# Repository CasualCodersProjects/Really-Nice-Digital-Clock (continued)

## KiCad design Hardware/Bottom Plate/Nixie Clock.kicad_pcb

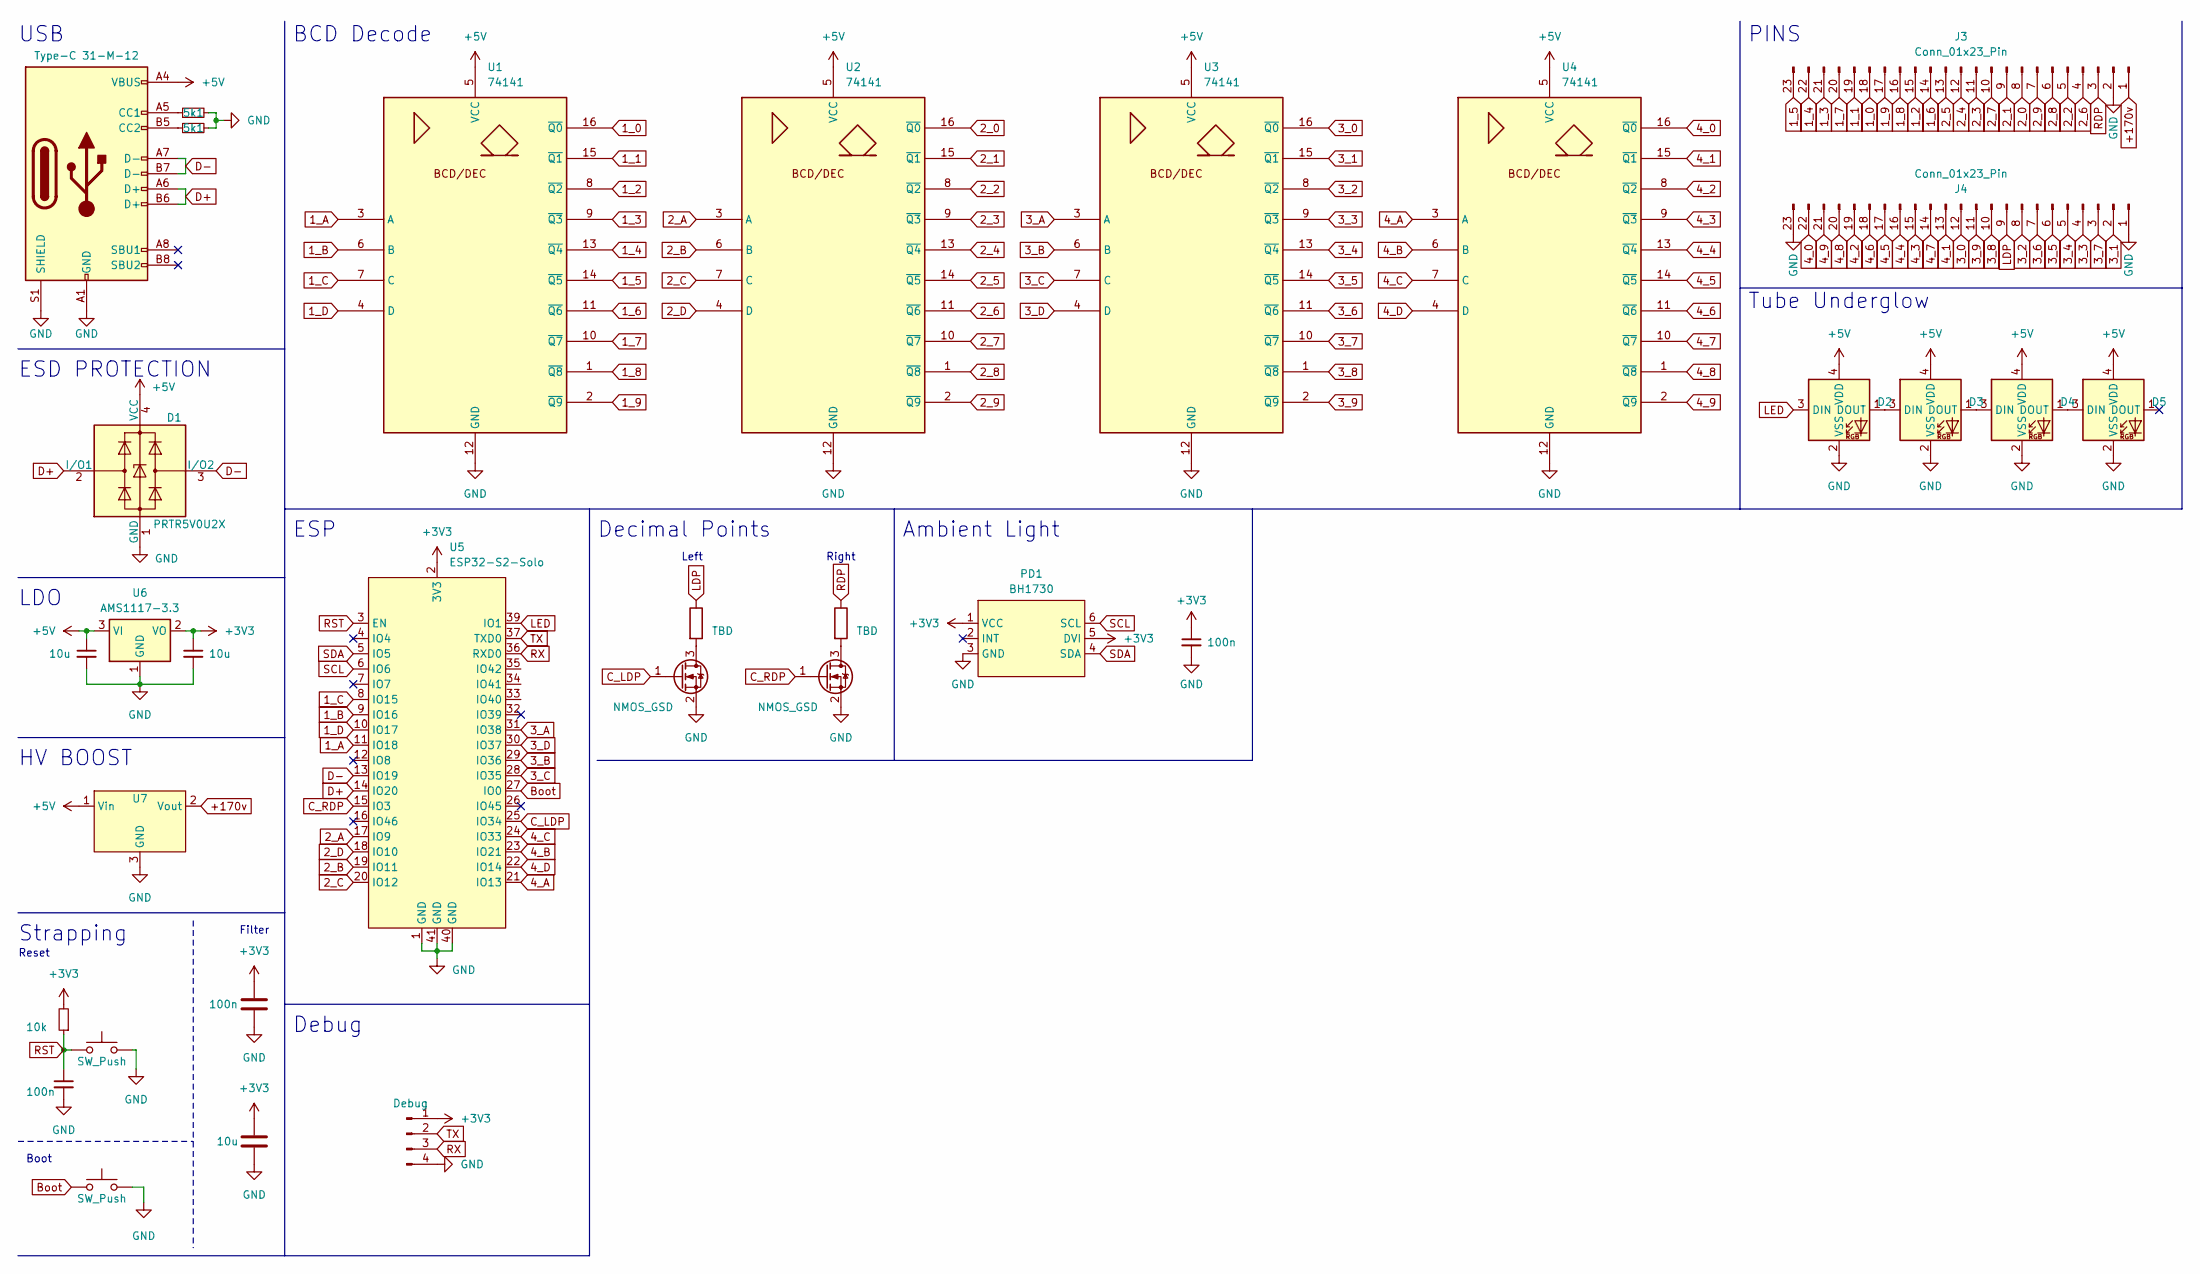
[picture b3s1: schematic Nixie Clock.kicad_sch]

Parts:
C1, C2, C3: 10u; C_0603_1608Metric
C4, C5, C6: 100n; C_0402_1005Metric
D1: PRTR5V0U2X; SOT-143
D2, D3, D4, D5: LED_WS2812B-2020_PLCC4_2.0x2.0mm
J1: Type-C 31-M-12; USB_C_Receptacle_HRO_TYPE-C-31-M-12
J2: Debug; PinHeader_1x04_P2.54mm_Vertical
J3, J4: Conn_01x23_Pin; PinSocket_1x23_P2.54mm_Vertical
PD1: BH1730; WSOF6
Q1, Q2: NMOS_GSD; SOT-23
R1, R2: 5k1; R_0402_1005Metric
R3: 10k; R_0402_1005Metric
R4, R5: TBD; R_0603_1608Metric_Pad0.98x0.95mm_HandSolder
RST1: SW_Push; SW_SPST_SKQG_WithStem
SW2: SW_Push; SW_SPST_SKQG_WithStem
U1, U2, U3, U4: 74141; DIP-16_W7.62mm
U5: ESP32-S2-Solo; ESP32-S3-WROOM-1
U6: AMS1117-3.3; SOT-223-3_TabPin2
U7: 8200HV

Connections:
1_0: J3.18, U1.16 (~Q0)
1_1: J3.19, U1.15 (~Q1)
1_2: J3.15, U1.8 (~Q2)
1_3: J3.21, U1.9 (~Q3)
1_4: J3.22, U1.13 (~Q4)
1_5: J3.23, U1.14 (~Q5)
1_6: J3.14, U1.11 (~Q6)
1_7: J3.20, U1.10 (~Q7)
1_8: J3.16, U1.1 (~Q8)
1_9: J3.17, U1.2 (~Q9)
1_A: U1.3 (A), U5.11 (IO18)
1_B: U1.6 (B), U5.9 (IO16)
1_C: U1.7 (C), U5.8 (IO15)
1_D: U1.4 (D), U5.10 (IO17)
2_0: J3.8, U2.16 (~Q0)
2_1: J3.9, U2.15 (~Q1)
2_2: J3.5, U2.8 (~Q2)
2_3: J3.11, U2.9 (~Q3)
2_4: J3.12, U2.13 (~Q4)
2_5: J3.13, U2.14 (~Q5)
2_6: J3.4, U2.11 (~Q6)
2_7: J3.10, U2.10 (~Q7)
2_8: J3.6, U2.1 (~Q8)
2_9: J3.7, U2.2 (~Q9)
2_A: U2.3 (A), U5.17 (IO9)
2_B: U2.6 (B), U5.19 (IO11)
2_C: U2.7 (C), U5.20 (IO12)
2_D: U2.4 (D), U5.18 (IO10)
3_0: J4.12, U3.16 (~Q0)
3_1: J4.2, U3.15 (~Q1)
3_2: J4.8, U3.8 (~Q2)
3_3: J4.4, U3.9 (~Q3)
3_4: J4.5, U3.13 (~Q4)
3_5: J4.6, U3.14 (~Q5)
3_6: J4.7, U3.11 (~Q6)
3_7: J4.3, U3.10 (~Q7)
3_8: J4.10, U3.1 (~Q8)
3_9: J4.11, U3.2 (~Q9)
3_A: U3.3 (A), U5.31 (IO38)
3_B: U3.6 (B), U5.29 (IO36)
3_C: U3.7 (C), U5.28 (IO35)
3_D: U3.4 (D), U5.30 (IO37)
4_0: J4.22, U4.16 (~Q0)
4_1: J4.13, U4.15 (~Q1)
4_2: J4.19, U4.8 (~Q2)
4_3: J4.15, U4.9 (~Q3)
4_4: J4.16, U4.13 (~Q4)
4_5: J4.17, U4.14 (~Q5)
4_6: J4.18, U4.11 (~Q6)
4_7: J4.14, U4.10 (~Q7)
4_8: J4.20, U4.1 (~Q8)
4_9: J4.21, U4.2 (~Q9)
4_A: U4.3 (A), U5.21 (IO13)
4_B: U4.6 (B), U5.23 (IO21)
4_C: U4.7 (C), U5.24 (IO33)
4_D: U4.4 (D), U5.22 (IO14)
+3V3: C2.1, C3.1, C4.1, C6.1, J2.1, PD1.1 (VCC), PD1.5 (DVI), R3.2, U5.2 (3V3), U6.2 (VO)
+5V: C1.1, D1.4 (VCC), D2.4 (VDD), D3.4 (VDD), D4.4 (VDD), D5.4 (VDD), J1.A4 (VBUS), J1.A9 (VBUS), J1.B4 (VBUS), J1.B9 (VBUS), U1.5 (VCC), U2.5 (VCC), U3.5 (VCC), U4.5 (VCC), U6.3 (VI), U7.1 (Vin)
+170v: J3.1, U7.2 (Vout)
C_LDP: Q2.1 (G), U5.25 (IO34)
C_RDP: Q1.1 (G), U5.15 (IO3)
D+: D1.2 (I/O1), J1.A6 (D+), J1.B6 (D+), U5.14 (IO20)
D-: D1.3 (I/O2), J1.A7 (D-), J1.B7 (D-), U5.13 (IO19)
GND: C1.2, C2.2, C3.2, C4.2, C5.2, C6.2, D1.1 (GND), D2.2 (VSS), D3.2 (VSS), D4.2 (VSS), D5.2 (VSS), J1.A1 (GND), J1.A12 (GND), J1.B1 (GND), J1.B12 (GND), J1.S1 (SHIELD), J2.4, J3.2, J4.1, J4.23, PD1.3 (GND), Q1.2 (S), Q2.2 (S), R1.2, R2.2, SW2.2, U1.12 (GND), U2.12 (GND), U3.12 (GND), U4.12 (GND), U5.1 (GND), U5.40 (GND), U5.41 (GND), U6.1 (GND), U7.3 (GND); also elsewhere on the board
LDP: J4.9, R5.1
LED: D2.3 (DIN), U5.39 (IO1)
unnamed: D2.1 (DOUT), D3.3 (DIN)
unnamed: D3.1 (DOUT), D4.3 (DIN)
unnamed: D4.1 (DOUT), D5.3 (DIN)
unnamed: J1.A5 (CC1), R1.1
unnamed: J1.B5 (CC2), R2.1
unnamed: Q1.3 (D), R4.2
unnamed: Q2.3 (D), R5.2
RDP: J3.3, R4.1
RX: J2.3, U5.36 (RXD0)
SCL: PD1.6 (SCL), U5.6 (IO6)
SDA: PD1.4 (SDA), U5.5 (IO5)
TX: J2.2, U5.37 (TXD0)

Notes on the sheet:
USB
Right
ESP
LDO
Strapping
Tube Underglow
Boot
HV BOOST
Reset
BCD Decode
Left
PINS
Decimal Points
Filter
Ambient Light
Debug
ESD PROTECTION

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
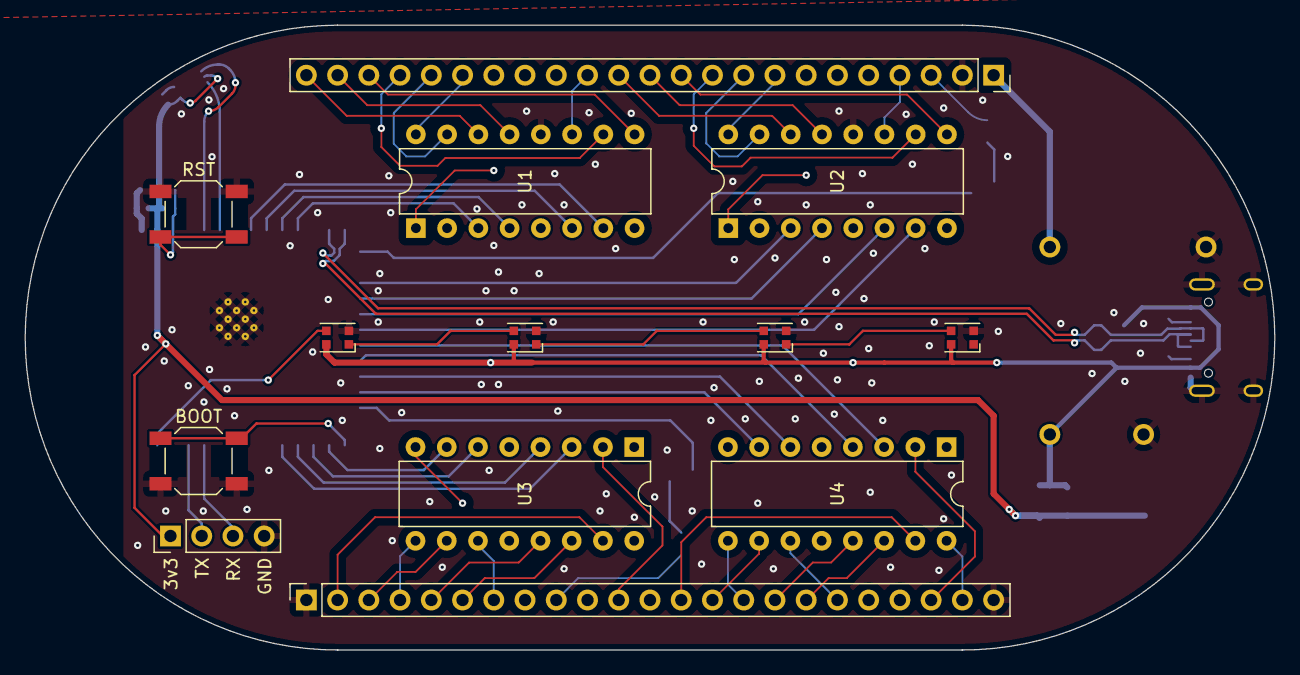
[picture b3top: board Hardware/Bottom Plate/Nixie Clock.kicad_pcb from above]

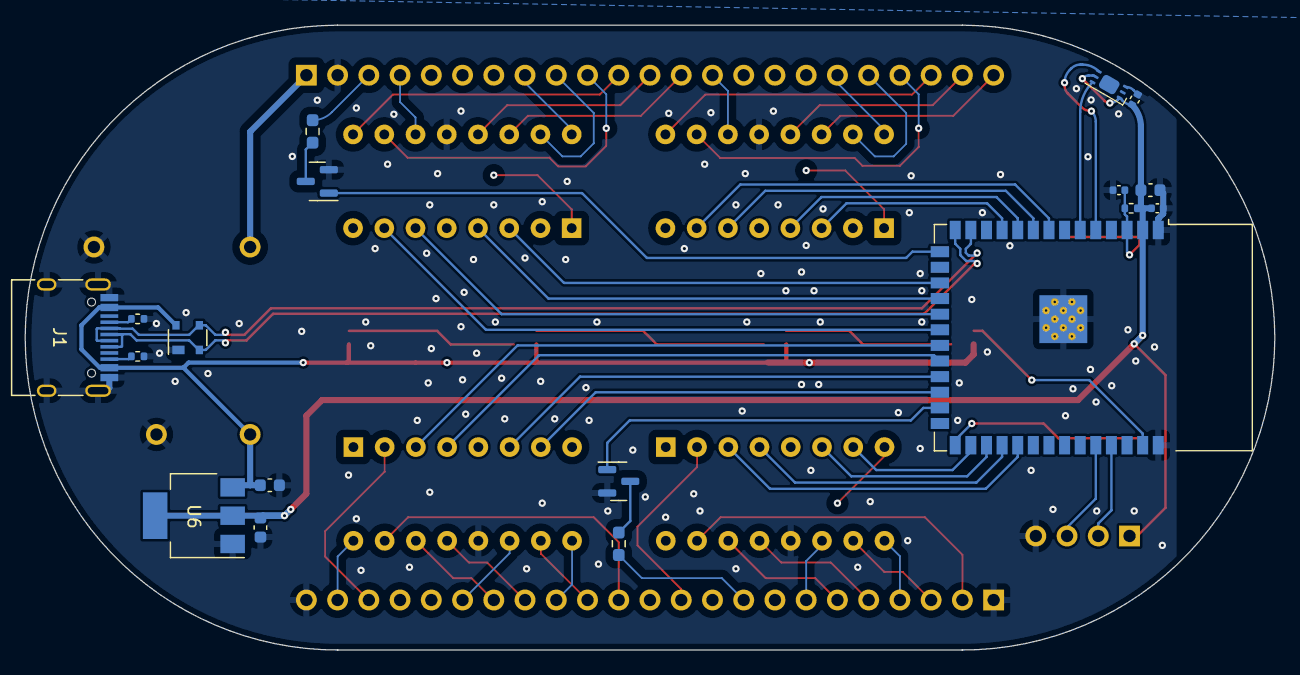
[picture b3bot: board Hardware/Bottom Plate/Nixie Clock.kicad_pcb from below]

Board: 4 copper layers, 101.6 x 50.8 mm, 32 parts (18 on the bottom side), 80 nets.

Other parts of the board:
SW1: SW_Push; SW_SPST_SKQG_WithStem

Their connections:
GND: SW1.2; also elsewhere on the board

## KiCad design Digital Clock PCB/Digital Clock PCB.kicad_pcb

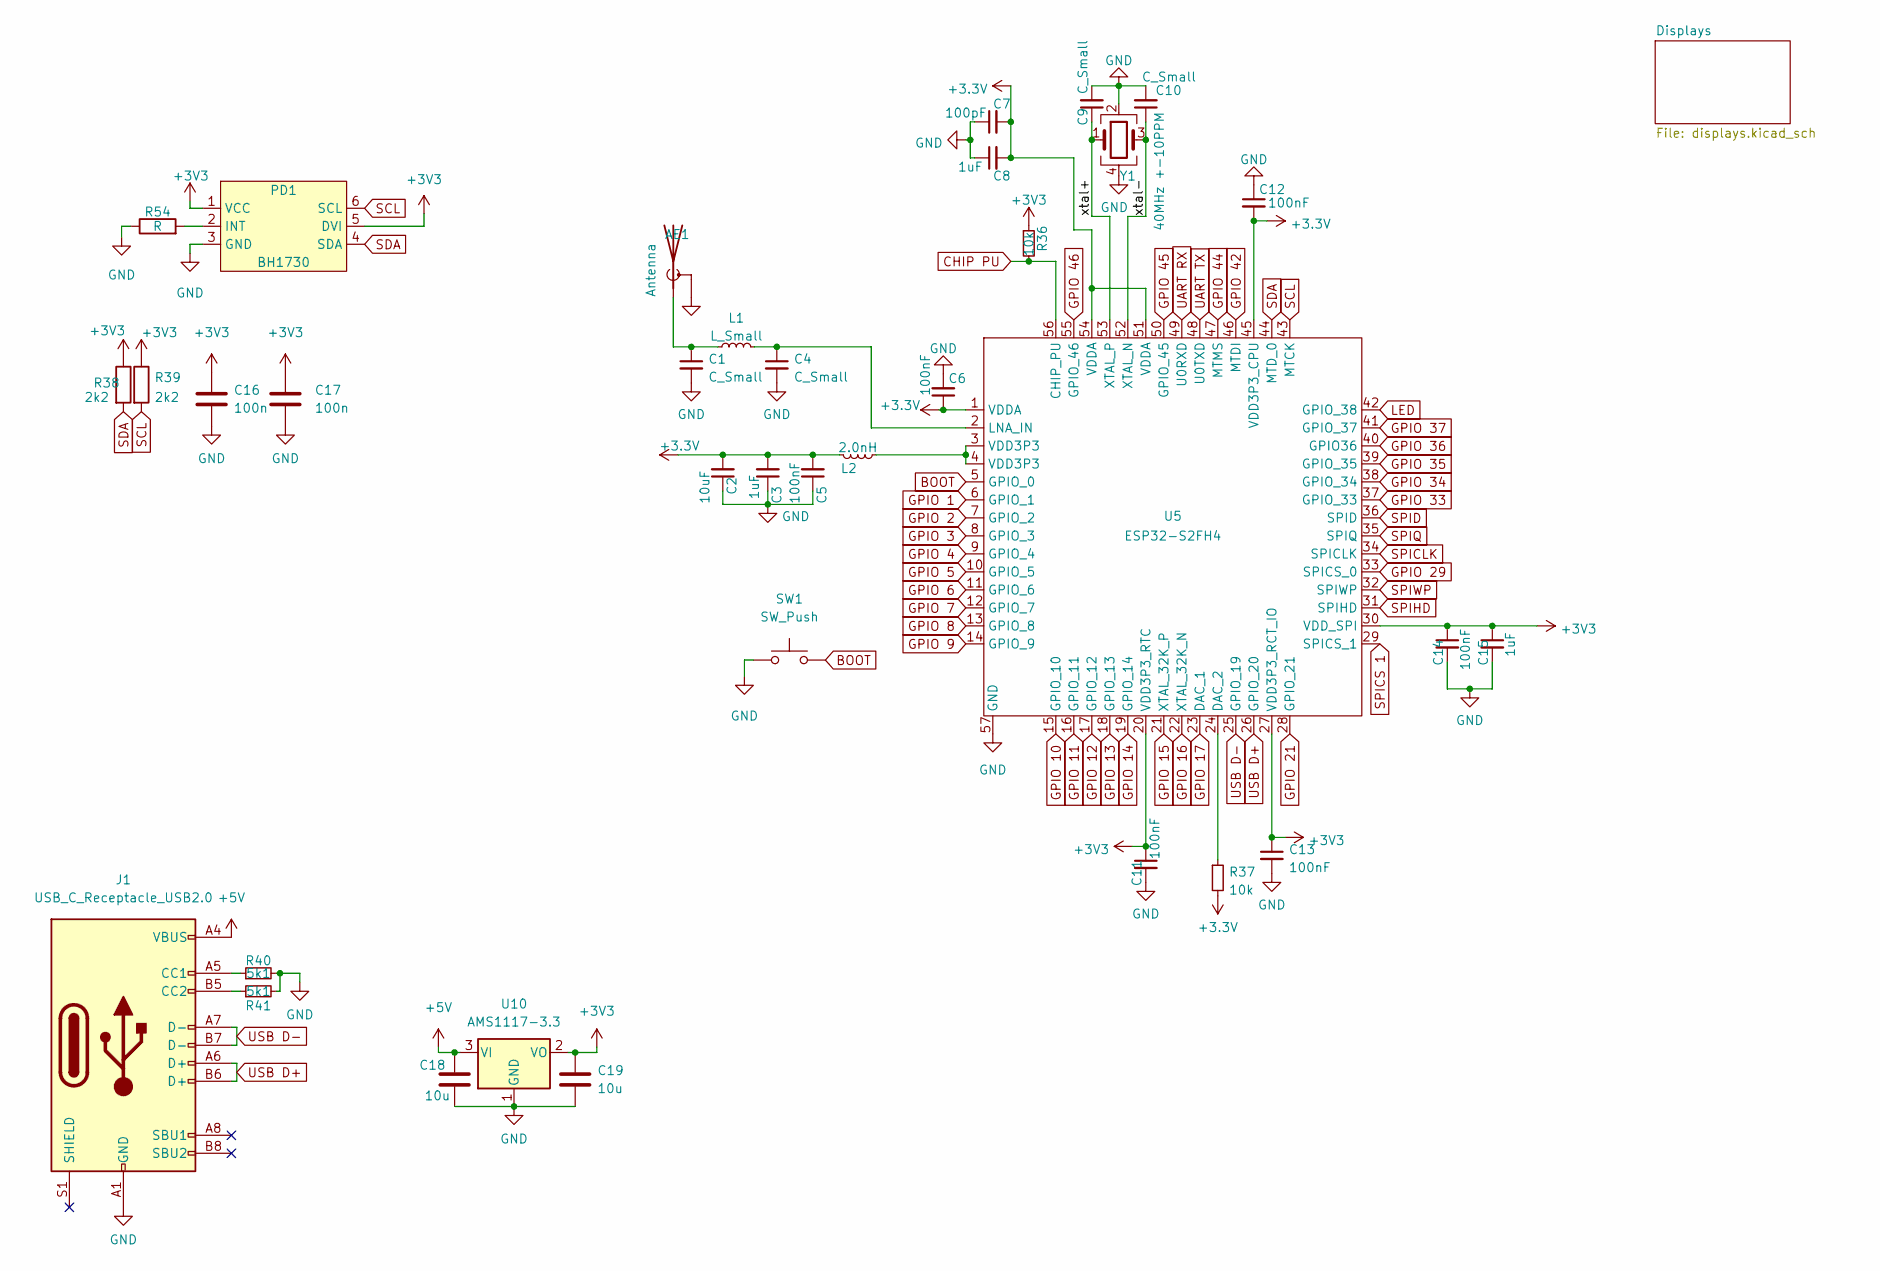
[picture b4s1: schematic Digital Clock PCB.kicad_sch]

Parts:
AE1: Antenna; Texas_SWRA117D_2.4GHz_Left
C1, C4, C9, C10: C_Small; C_0402_1005Metric
C2: 10uF; C_0603_1608Metric
C3, C8, C15: 1uF; C_0402_1005Metric
C5, C6, C11, C12, C13, C14: 100nF; C_0402_1005Metric
C7: 100pF; C_0402_1005Metric
C16, C17: 100n; C_0402_1005Metric
C18, C19: 10u; C_0603_1608Metric
J1: USB_C_Receptacle_USB2.0; USB_C_Receptacle_HRO_TYPE-C-31-M-12
L1: L_Small; L_0402_1005Metric
L2: 2.0nH; L_0402_1005Metric
PD1: BH1730; WSOF6
R36, R37: 10k; R_0402_1005Metric
R38, R39: 2k2; R_0402_1005Metric
R40, R41: 5k1; R_0402_1005Metric
R54: R; R_0402_1005Metric
SW1: SW_Push; 5.2mm_Tactile_Push_Button
U5: ESP32-S2FH4; ESP32-S2
U10: AMS1117-3.3; SOT-223-3_TabPin2
Y1: 40MHz +-10PPM; Crystal_SMD_2520-4Pin_2.5x2.0mm

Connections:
+5V: C18.1, J1.A4 (VBUS), J1.A9 (VBUS), J1.B4 (VBUS), J1.B9 (VBUS), U10.3 (VI); also elsewhere on the board
/xtal+: C9.1, U5.53 (XTAL_P), Y1.1
/xtal-: C10.1, U5.52 (XTAL_N), Y1.3
BOOT: SW1.2, U5.5 (GPIO_0)
CHIP PU: R36.2, U5.56 (CHIP_PU)
GND: AE1.2 (Shield), C1.2, C2.1, C3.1, C4.2, C5.1, C6.2, C7.1, C8.1, C9.2, C10.2, C11.2, C12.1, C13.2, C14.2, C15.2, C16.2, C17.2, C18.2, C19.2, J1.A1 (GND), J1.A12 (GND), J1.B1 (GND), J1.B12 (GND), PD1.3 (GND), R40.2, R41.2, R54.1, SW1.1, U5.57 (GND), U10.1 (GND), Y1.2, Y1.4; also elsewhere on the board
GPIO 1: U5.6 (GPIO_1); also elsewhere on the board
GPIO 2: U5.7 (GPIO_2); also elsewhere on the board
GPIO 3: U5.8 (GPIO_3); also elsewhere on the board
GPIO 4: U5.9 (GPIO_4); also elsewhere on the board
GPIO 5: U5.10 (GPIO_5); also elsewhere on the board
GPIO 6: U5.11 (GPIO_6); also elsewhere on the board
GPIO 7: U5.12 (GPIO_7); also elsewhere on the board
GPIO 8: U5.13 (GPIO_8); also elsewhere on the board
GPIO 9: U5.14 (GPIO_9); also elsewhere on the board
GPIO 10: U5.15 (GPIO_10); also elsewhere on the board
GPIO 11: U5.16 (GPIO_11); also elsewhere on the board
GPIO 12: U5.17 (GPIO_12); also elsewhere on the board
GPIO 13: U5.18 (GPIO_13); also elsewhere on the board
GPIO 14: U5.19 (GPIO_14); also elsewhere on the board
GPIO 15: U5.21 (XTAL_32K_P); also elsewhere on the board
GPIO 16: U5.22 (XTAL_32K_N); also elsewhere on the board
GPIO 17: U5.23 (DAC_1)
GPIO 21: U5.28 (GPIO_21); also elsewhere on the board
GPIO 29: U5.33 (SPICS_0)
GPIO 33: U5.37 (GPIO_33); also elsewhere on the board
GPIO 34: U5.38 (GPIO_34); also elsewhere on the board
GPIO 35: U5.39 (GPIO_35); also elsewhere on the board
GPIO 36: U5.40 (GPIO36)
GPIO 37: U5.41 (GPIO_37)
GPIO 42: U5.46 (MTDI)
GPIO 44: U5.47 (MTMS)
GPIO 45: U5.50 (GPIO_45)
GPIO 46: U5.55 (GPIO_46)
LED: U5.42 (GPIO_38); also elsewhere on the board
unnamed: AE1.1 (A), C1.1, L1.1
unnamed: C4.1, L1.2, U5.2 (LNA_IN)
unnamed: J1.A5 (CC1), R40.1
unnamed: J1.B5 (CC2), R41.1
unnamed: L2.1, U5.3 (VDD3P3), U5.4 (VDD3P3)
unnamed: PD1.2 (INT), R54.2
unnamed: R37.1, U5.24 (DAC_2)
SCL: PD1.6 (SCL), R39.2, U5.43 (MTCK)
SDA: PD1.4 (SDA), R38.2, U5.44 (MTD_0)
SPICLK: U5.34 (SPICLK)
SPICS 1: U5.29 (SPICS_1)
SPID: U5.36 (SPID)
SPIHD: U5.31 (SPIHD)
SPIQ: U5.35 (SPIQ)
SPIWP: U5.32 (SPIWP)
UART RX: U5.49 (U0RXD)
UART TX: U5.48 (U0TXD)
USB D+: J1.A6 (D+), J1.B6 (D+), U5.26 (GPIO_20)
USB D-: J1.A7 (D-), J1.B7 (D-), U5.25 (GPIO_19)

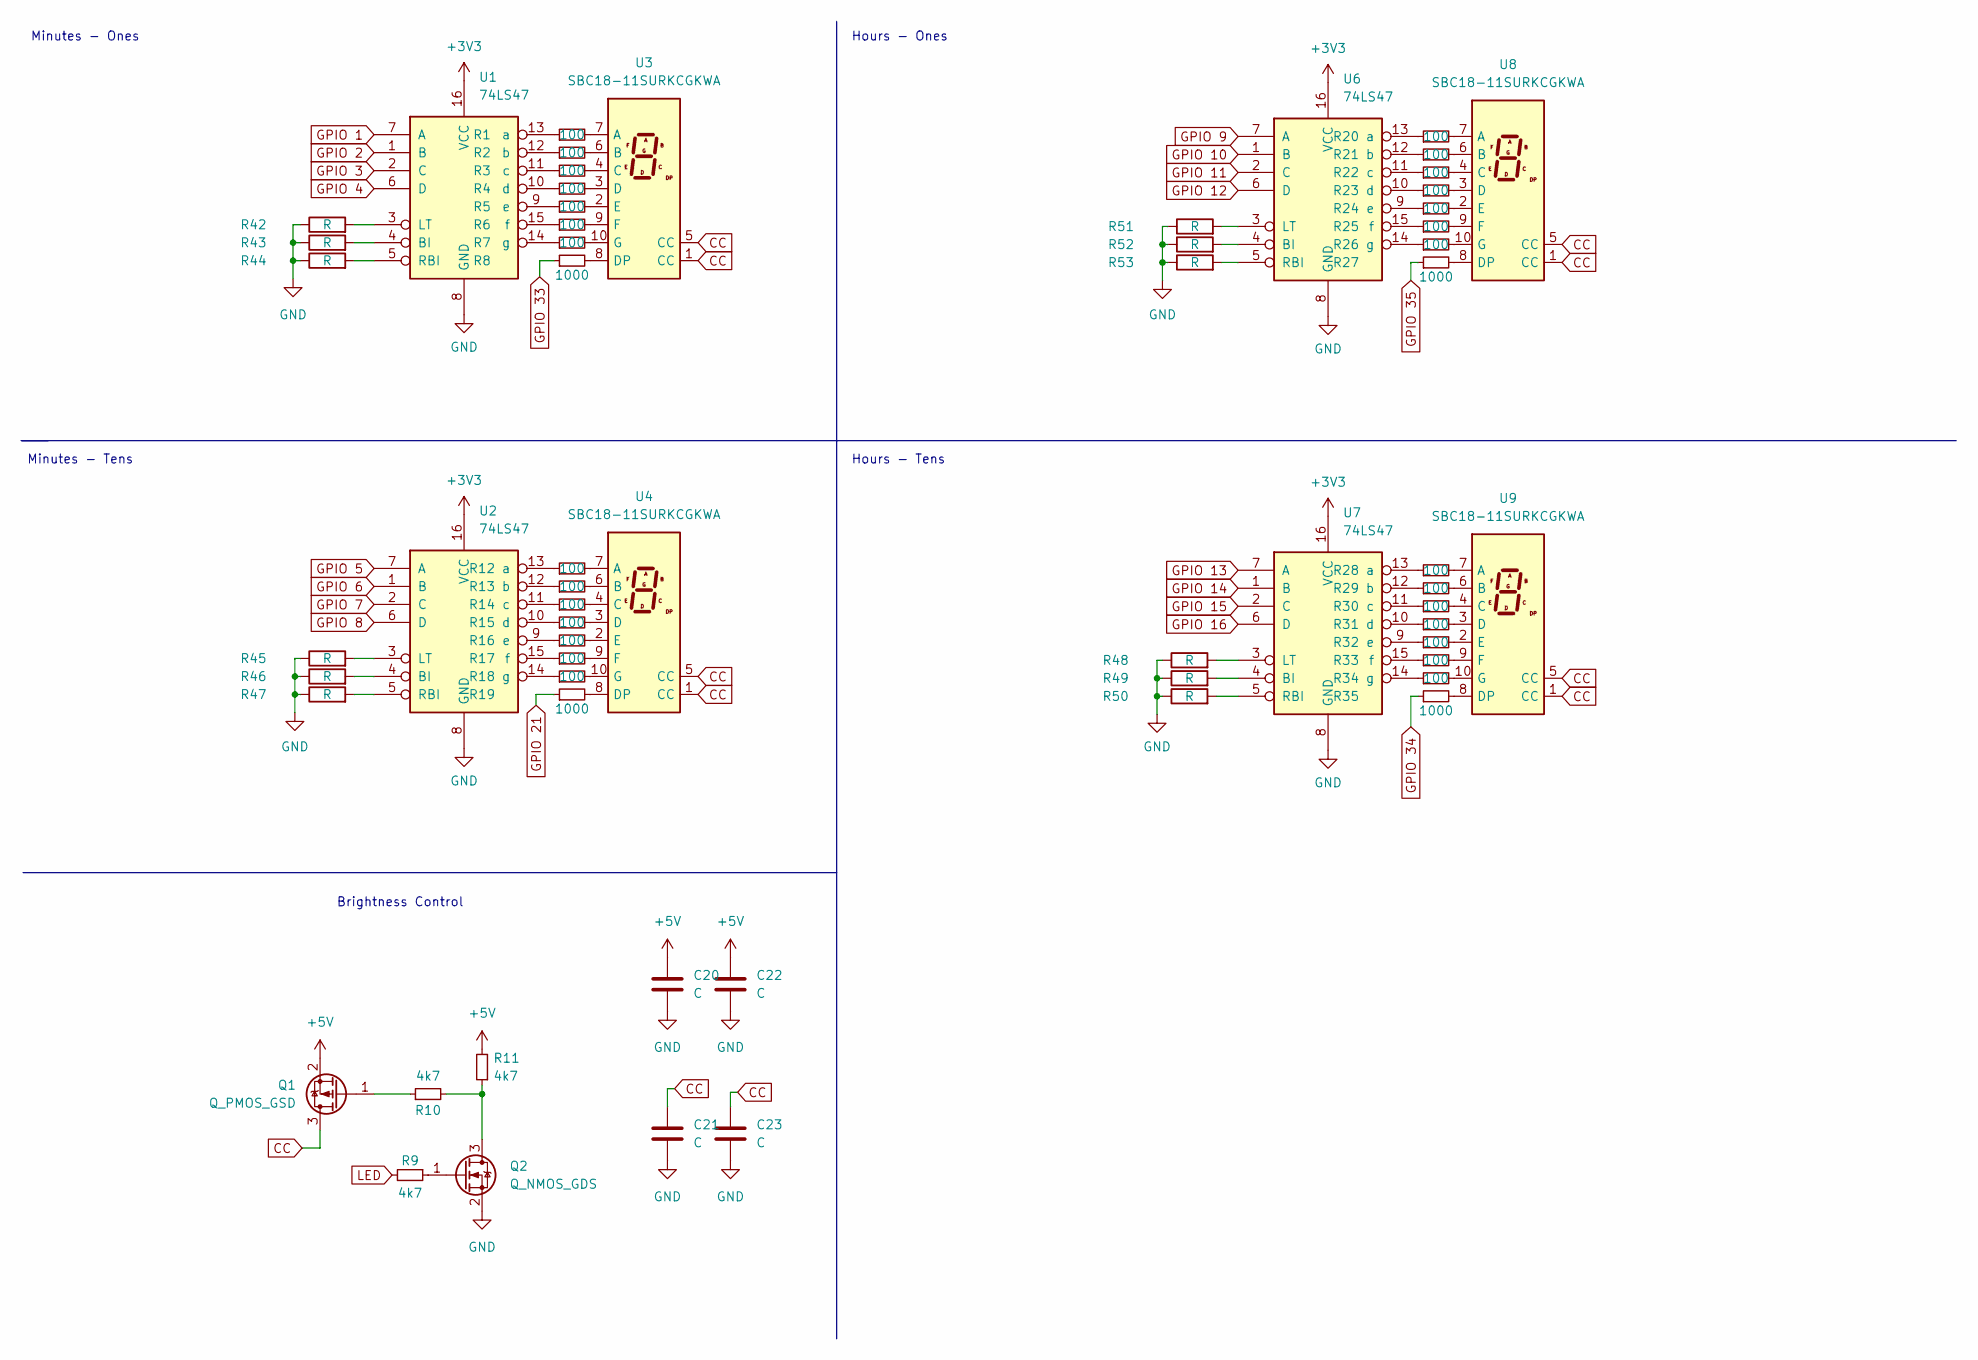
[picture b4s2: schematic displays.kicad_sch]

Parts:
C20, C21, C22, C23: C; C_0603_1608Metric_Pad1.08x0.95mm_HandSolder
Q1: Q_PMOS_GSD; SOT-523
Q2: Q_NMOS_GDS; SOT-523
R1, R2, R3, R4, R5, R6, R7, R12, R13, R14, R15, R16, R17, R18, R20, R21, R22, R23, R24, R25, R26, R28, R29, R30, R31, R32, R33, R34: 100; R_0402_1005Metric
R8, R19, R27, R35: 1000; R_0402_1005Metric
R9, R10, R11: 4k7; R_0402_1005Metric
R42, R43, R44, R45, R46, R47, R48, R49, R50, R51, R52, R53: R; R_0603_1608Metric
U1, U2, U6, U7: 74LS47; SOIC-16_4.55x10.3mm_P1.27mm
U3, U4, U8, U9: SBC18-11SURKCGKWA; Segment_Display_1-5_inch

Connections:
+5V: C20.1, C22.1, Q1.2 (S), R11.2; also elsewhere on the board
CC: C21.1, C23.1, Q1.3 (D), U3.1 (CC), U3.5 (CC), U4.1 (CC), U4.5 (CC), U8.1 (CC), U8.5 (CC), U9.1 (CC), U9.5 (CC)
GND: C20.2, C21.2, C22.2, C23.2, Q2.2 (S), R42.1, R43.1, R44.1, R45.1, R46.1, R47.1, R48.1, R49.1, R50.1, R51.1, R52.1, R53.1, U1.8 (GND), U2.8 (GND), U6.8 (GND), U7.8 (GND); also elsewhere on the board
GPIO 1: U1.7 (A); also elsewhere on the board
GPIO 2: U1.1 (B); also elsewhere on the board
GPIO 3: U1.2 (C); also elsewhere on the board
GPIO 4: U1.6 (D); also elsewhere on the board
GPIO 5: U2.7 (A); also elsewhere on the board
GPIO 6: U2.1 (B); also elsewhere on the board
GPIO 7: U2.2 (C); also elsewhere on the board
GPIO 8: U2.6 (D); also elsewhere on the board
GPIO 9: U6.7 (A); also elsewhere on the board
GPIO 10: U6.1 (B); also elsewhere on the board
GPIO 11: U6.2 (C); also elsewhere on the board
GPIO 12: U6.6 (D); also elsewhere on the board
GPIO 13: U7.7 (A); also elsewhere on the board
GPIO 14: U7.1 (B); also elsewhere on the board
GPIO 15: U7.2 (C); also elsewhere on the board
GPIO 16: U7.6 (D); also elsewhere on the board
GPIO 21: R19.1; also elsewhere on the board
GPIO 33: R8.1; also elsewhere on the board
GPIO 34: R35.1; also elsewhere on the board
GPIO 35: R27.1; also elsewhere on the board
LED: R9.2; also elsewhere on the board
unnamed: Q1.1 (G), R10.1
unnamed: R1.1, U1.13 (a)
unnamed: R1.2, U3.7 (A)
unnamed: R2.1, U1.12 (b)
unnamed: R2.2, U3.6 (B)
unnamed: R3.1, U1.11 (c)
unnamed: R3.2, U3.4 (C)
unnamed: R4.1, U1.10 (d)
unnamed: R4.2, U3.3 (D)
unnamed: R5.1, U1.9 (e)
unnamed: R5.2, U3.2 (E)
unnamed: R6.1, U1.15 (f)
unnamed: R6.2, U3.9 (F)
unnamed: R7.1, U1.14 (g)
unnamed: R7.2, U3.10 (G)
unnamed: R8.2, U3.8 (DP)
unnamed: Q2.1 (G), R9.1
unnamed: Q2.3 (D), R10.2, R11.1
unnamed: R12.1, U2.13 (a)
unnamed: R12.2, U4.7 (A)
unnamed: R13.1, U2.12 (b)
unnamed: R13.2, U4.6 (B)
unnamed: R14.1, U2.11 (c)
unnamed: R14.2, U4.4 (C)
unnamed: R15.1, U2.10 (d)
unnamed: R15.2, U4.3 (D)
unnamed: R16.1, U2.9 (e)
unnamed: R16.2, U4.2 (E)
unnamed: R17.1, U2.15 (f)
unnamed: R17.2, U4.9 (F)
unnamed: R18.1, U2.14 (g)
unnamed: R18.2, U4.10 (G)
unnamed: R19.2, U4.8 (DP)
unnamed: R20.1, U6.13 (a)
unnamed: R20.2, U8.7 (A)
unnamed: R21.1, U6.12 (b)
unnamed: R21.2, U8.6 (B)
unnamed: R22.1, U6.11 (c)
unnamed: R22.2, U8.4 (C)
unnamed: R23.1, U6.10 (d)
unnamed: R23.2, U8.3 (D)
unnamed: R24.1, U6.9 (e)
unnamed: R24.2, U8.2 (E)
unnamed: R25.1, U6.15 (f)
unnamed: R25.2, U8.9 (F)
unnamed: R26.1, U6.14 (g)
unnamed: R26.2, U8.10 (G)
unnamed: R27.2, U8.8 (DP)
unnamed: R28.1, U7.13 (a)
unnamed: R28.2, U9.7 (A)
unnamed: R29.1, U7.12 (b)
unnamed: R29.2, U9.6 (B)
unnamed: R30.1, U7.11 (c)
unnamed: R30.2, U9.4 (C)
unnamed: R31.1, U7.10 (d)
unnamed: R31.2, U9.3 (D)
unnamed: R32.1, U7.9 (e)
unnamed: R32.2, U9.2 (E)
unnamed: R33.1, U7.15 (f)
unnamed: R33.2, U9.9 (F)
unnamed: R34.1, U7.14 (g)
unnamed: R34.2, U9.10 (G)
unnamed: R35.2, U9.8 (DP)
unnamed: R42.2, U1.3 (LT)
unnamed: R43.2, U1.4 (BI)
unnamed: R44.2, U1.5 (RBI)
unnamed: R45.2, U2.3 (LT)
unnamed: R46.2, U2.4 (BI)
unnamed: R47.2, U2.5 (RBI)
unnamed: R48.2, U7.3 (LT)
unnamed: R49.2, U7.4 (BI)
unnamed: R50.2, U7.5 (RBI)
unnamed: R51.2, U6.3 (LT)
unnamed: R52.2, U6.4 (BI)
unnamed: R53.2, U6.5 (RBI)

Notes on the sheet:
Hours - Ones
Hours - Tens
Minutes - Ones
Brightness Control
Minutes - Tens

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
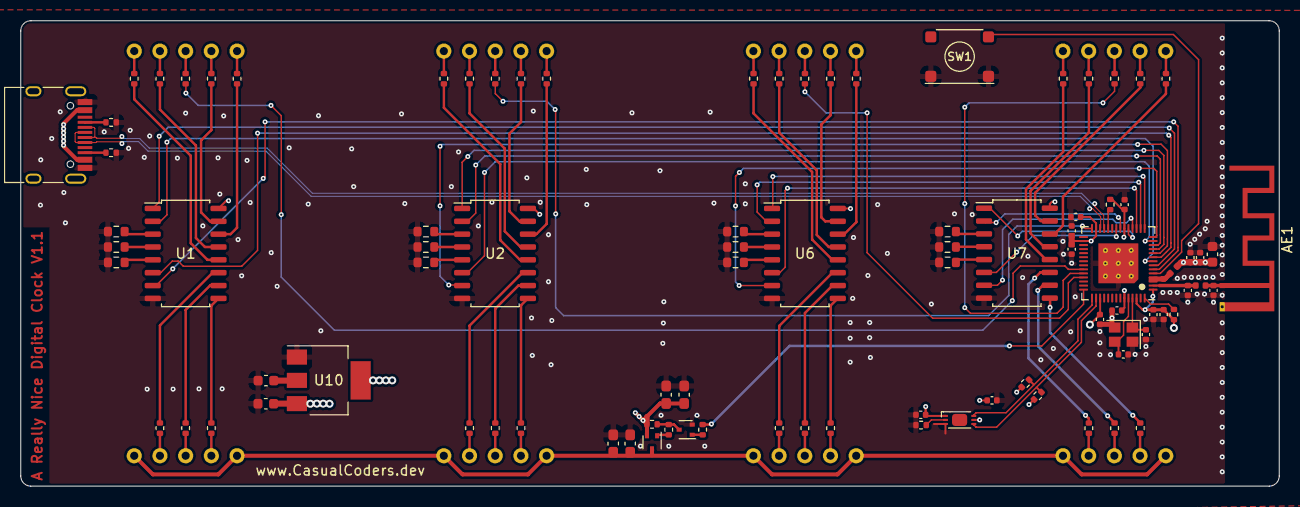
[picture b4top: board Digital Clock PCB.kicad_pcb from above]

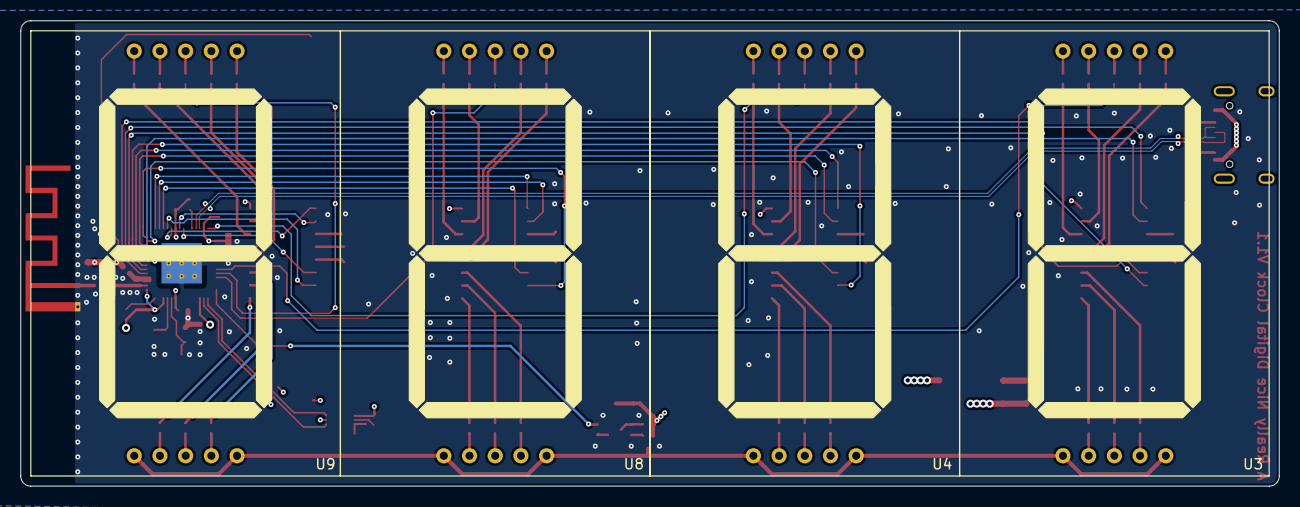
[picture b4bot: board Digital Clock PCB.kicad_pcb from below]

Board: 4 copper layers, 124.4 x 46.0 mm, 96 parts (4 on the bottom side), 115 nets.

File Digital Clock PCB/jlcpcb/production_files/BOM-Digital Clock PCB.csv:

Comment,Designator,Footprint,LCSC
1000,"R19,R27,R35,R8",R_0402_1005Metric,C11702
L_Small,L1,L_0402_1005Metric,C1330149
100nF,"C11,C12,C13,C14,C16,C17,C5,C6,C7",C_0402_1005Metric,C1525
C_Small,"C10,C9",C_0402_1005Metric,C1547
USB_C_Receptacle_USB2.0,J1,USB_C_Receptacle_HRO_TYPE-C-31-M-12,C165948
100,"R1,R12,R13,R14,R15,R16,R17,R18,R2,R20,R21,R22,R23,R24,R25,R26,R28,R29,R3,R30,R31,R32,R33,R34,R4,R5,R6,R7",R_0402_1005Metric,C25076
10k,"R36,R37",R_0402_1005Metric,C25744
4k7,"R10,R11,R9",R_0402_1005Metric,C25900
5k1,"R40,R41",R_0402_1005Metric,C25905
ESP32-S2FH4,U5,ESP32-S2,C2840995
Q_PMOS_GSD,"Q1,Q2",SOT-523,C2879716
74LS47,"U1,U2,U6,U7",SOIC-16_4.55x10.3mm_P1.27mm,C356693
2.0nH,L2,L_0402_1005Metric,C361506
1uF,"C15,C3,C8",C_0402_1005Metric,C52923
AMS1117-3.3,U10,SOT-223-3_TabPin2,C6186
C_Small,"C1,C4",C_0402_1005Metric,C76914
BH1730,PD1,WSOF6,C79616
40MHz +-10PPM,Y1,Crystal_SMD_2520-4Pin_2.5x2.0mm,C90925
10u,"C18,C19,C2",C_0603_1608Metric,C96446
C,C21,C_0603_1608Metric_Pad1.08x0.95mm_HandSolder,
R,R47,R_0603_1608Metric,
R,R53,R_0603_1608Metric,
SW_Push,SW1,5.2mm_Tactile_Push_Button,
R,R44,R_0603_1608Metric,
R,R45,R_0603_1608Metric,
R,R46,R_0603_1608Metric,
R,R50,R_0603_1608Metric,
R,R54,R_0402_1005Metric,
C,C20,C_0603_1608Metric_Pad1.08x0.95mm_HandSolder,
Antenna,AE1,Texas_SWRA117D_2.4GHz_Left,
2k2,R38,R_0402_1005Metric,
C,C23,C_0603_1608Metric_Pad1.08x0.95mm_HandSolder,
R,R42,R_0603_1608Metric,
R,R48,R_0603_1608Metric,
R,R43,R_0603_1608Metric,
C,C22,C_0603_1608Metric_Pad1.08x0.95mm_HandSolder,
2k2,R39,R_0402_1005Metric,
R,R52,R_0603_1608Metric,
R,R49,R_0603_1608Metric,
R,R51,R_0603_1608Metric,
SBC18-11SURKCGKWA,U4,Segment_Display_1-5_inch,
SBC18-11SURKCGKWA,U9,Segment_Display_1-5_inch,
SBC18-11SURKCGKWA,U8,Segment_Display_1-5_inch,
SBC18-11SURKCGKWA,U3,Segment_Display_1-5_inch,

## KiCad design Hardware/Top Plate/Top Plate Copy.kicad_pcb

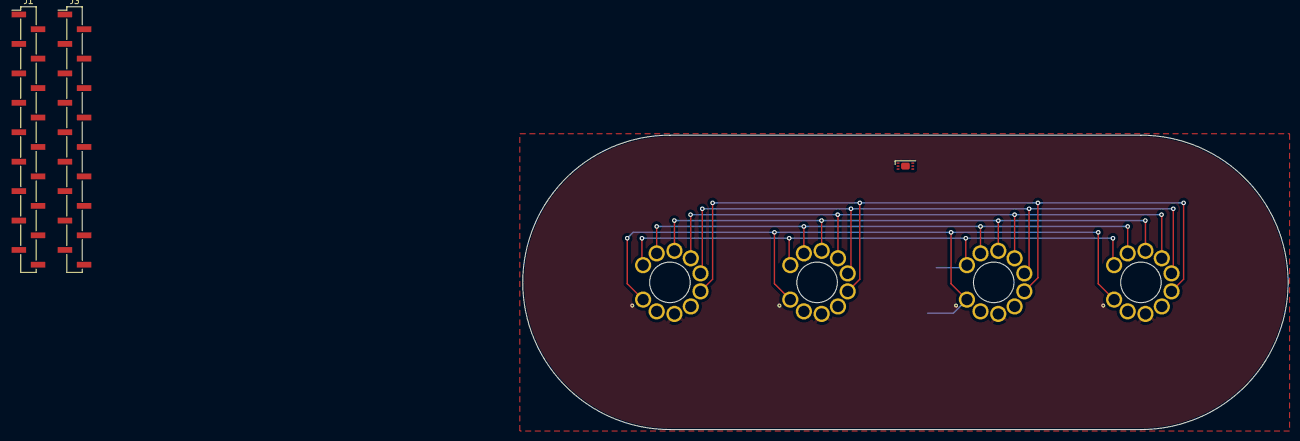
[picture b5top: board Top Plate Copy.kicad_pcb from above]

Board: 2 copper layers, 132.1 x 50.8 mm, 7 parts (1 on the bottom side), 10 nets.

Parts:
J1, J3: Conn_01x18_Pin; PinHeader_1x18_P2.54mm_Vertical_SMD_Pin1Left
U1, U2, U3, U4: IV-12
U5: PLCC-28

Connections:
+GRID: J3.1, U5.1 (VPP)
+HEATER: J1.18, U1.2 (K+), U2.2 (K+), U3.2 (K+), U4.2 (K+)
A: U1.8 (a), U2.8 (a), U3.8 (a), U4.8 (a), U5.22 (HV5)
B: U1.7 (b), U2.7 (b), U3.7 (b), U4.7 (b), U5.23 (HV4)
C: U1.6 (c), U2.6 (c), U3.6 (c), U4.6 (c), U5.24 (HV3)
D: U1.5 (d), U2.5 (d), U3.5 (d), U4.5 (d), U5.25 (HV2)
E: U1.1 (e), U2.1 (e), U3.1 (e), U4.1 (e), U5.26 (HV1)
F: U1.10 (f), U2.10 (f), U3.10 (f), U4.10 (f), U5.20 (HV7)
G: U1.9 (g), U2.9 (g), U3.9 (g), U4.9 (g), U5.21 (HV6)
GND: J1.8, J1.16, J1.17, J3.2, J3.3, J3.11, U1.3 (K-), U2.3 (K-), U3.3 (K-), U4.3 (K-), U5.14 (GND)

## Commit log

2023-06-26 Version 1.0 of the hardware and software
2023-06-26 add 3d printable case files
2023-06-26 Add Version 2.0 of the hardware and software
2023-06-26 Removed files that shouldn't be public
2023-10-02 Unknown changes. Something probably
2024-01-07 Use real timezone file, better autobrightness, method of viewing IP, Better web Interface.
2024-01-07 Updated Hardware and folder names
2024-01-07 Added a readme
2024-01-09 Correct spelling mistake. Rename folders.
2024-01-09 Removed unnecessary variables. Cleaned up code. A few more comments.
2024-01-09 Added note about remaining decimal points.
2024-01-09 spelling
2024-01-09 3D files and product images
2024-01-12 Create LICENSE
2024-01-13 Add cutout for antenna in case
2024-01-17 Revert main.cpp to real release code
2024-01-23 Custom Code for Podcast
2024-01-23 Complete firmware for podcast setup
2024-02-20 Start vfd PCB Layout and schema
2024-04-04 I think these are the files I submitted to JLC
2024-05-01 Something
2024-05-19 Move firmware down a directory. Add Integration test. Requires gitignored file containing wifi credentials.
2024-07-12 Update hourly instead of minutely. Oops.
2024-10-22 I think this is the most up to date version. It's possible that this is totally messed up.
